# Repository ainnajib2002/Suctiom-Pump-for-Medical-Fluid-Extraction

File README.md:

## Suction-Pump-for-Medical-Fluid-Extraction

# Suction Pump for Medical Fluid Extraction

## Deskripsi Proyek
Suction Pump adalah alat medis untuk menghisap berbagai jenis cairan tubuh seperti darah, lendir, dan nanah selama prosedur medis. Proyek ini dirancang untuk menghasilkan suction pump berbasis mikrokontroler Arduino Mega dengan fitur IoT, keypad, dan LCD untuk pemantauan dan kontrol yang lebih baik.

---

## Fitur Utama
- **IoT Integration**: Pemantauan dan kontrol jarak jauh melalui cloud.
- **User Interface**: Keypad 4x4 dan LCD 20x4 untuk pengoperasian mudah.
- **Safety Design**: Bahan stainless steel untuk ketahanan dan kebersihan.

---

## Alat dan Bahan
| Komponen            | Deskripsi                                                                 |
|---------------------|---------------------------------------------------------------------------|
| **Mikrokontroler**  | Arduino Mega                                                            |
| **Sensor**          | MPX 5700 untuk tekanan                                                  |
| **Komponen Elektrik**| LCD 20x4, Keypad Matrix 4x4, Driver Motor L298N, Potentiometer         |
| **Komponen Mekanikal**| Bahan stainless steel untuk casing dan komponen mekanis lainnya       |

---

## Desain 3D

## Skema Rangkaian

---

## Panduan Instalasi dan Penggunaan
1. **Persiapan Hardware**: 
   - Rakit semua komponen sesuai skema.
   - Pastikan koneksi ke ESP32 dan sistem mekanik sudah sesuai.
2. **Instalasi Software**:
   - Gunakan Arduino IDE untuk mengunggah kode ke mikrokontroler.
3. **Konfigurasi IoT**:
   - Masukkan detail WiFi melalui keypad untuk koneksi cloud.
4. **Pengoperasian**:
   - Gunakan keypad untuk mengatur kecepatan dan parameter operasi.
   - Pantau informasi pada LCD 20x4.

---

## Sumber
- [Arduino IDE](https://www.arduino.cc/en/software)
- [Komponen ESP32](https://www.espressif.com/en/products/socs/esp32)

---

Jika desain ini sudah sesuai, saya dapat menambahkan detail lainnya. Silakan beri tahu!

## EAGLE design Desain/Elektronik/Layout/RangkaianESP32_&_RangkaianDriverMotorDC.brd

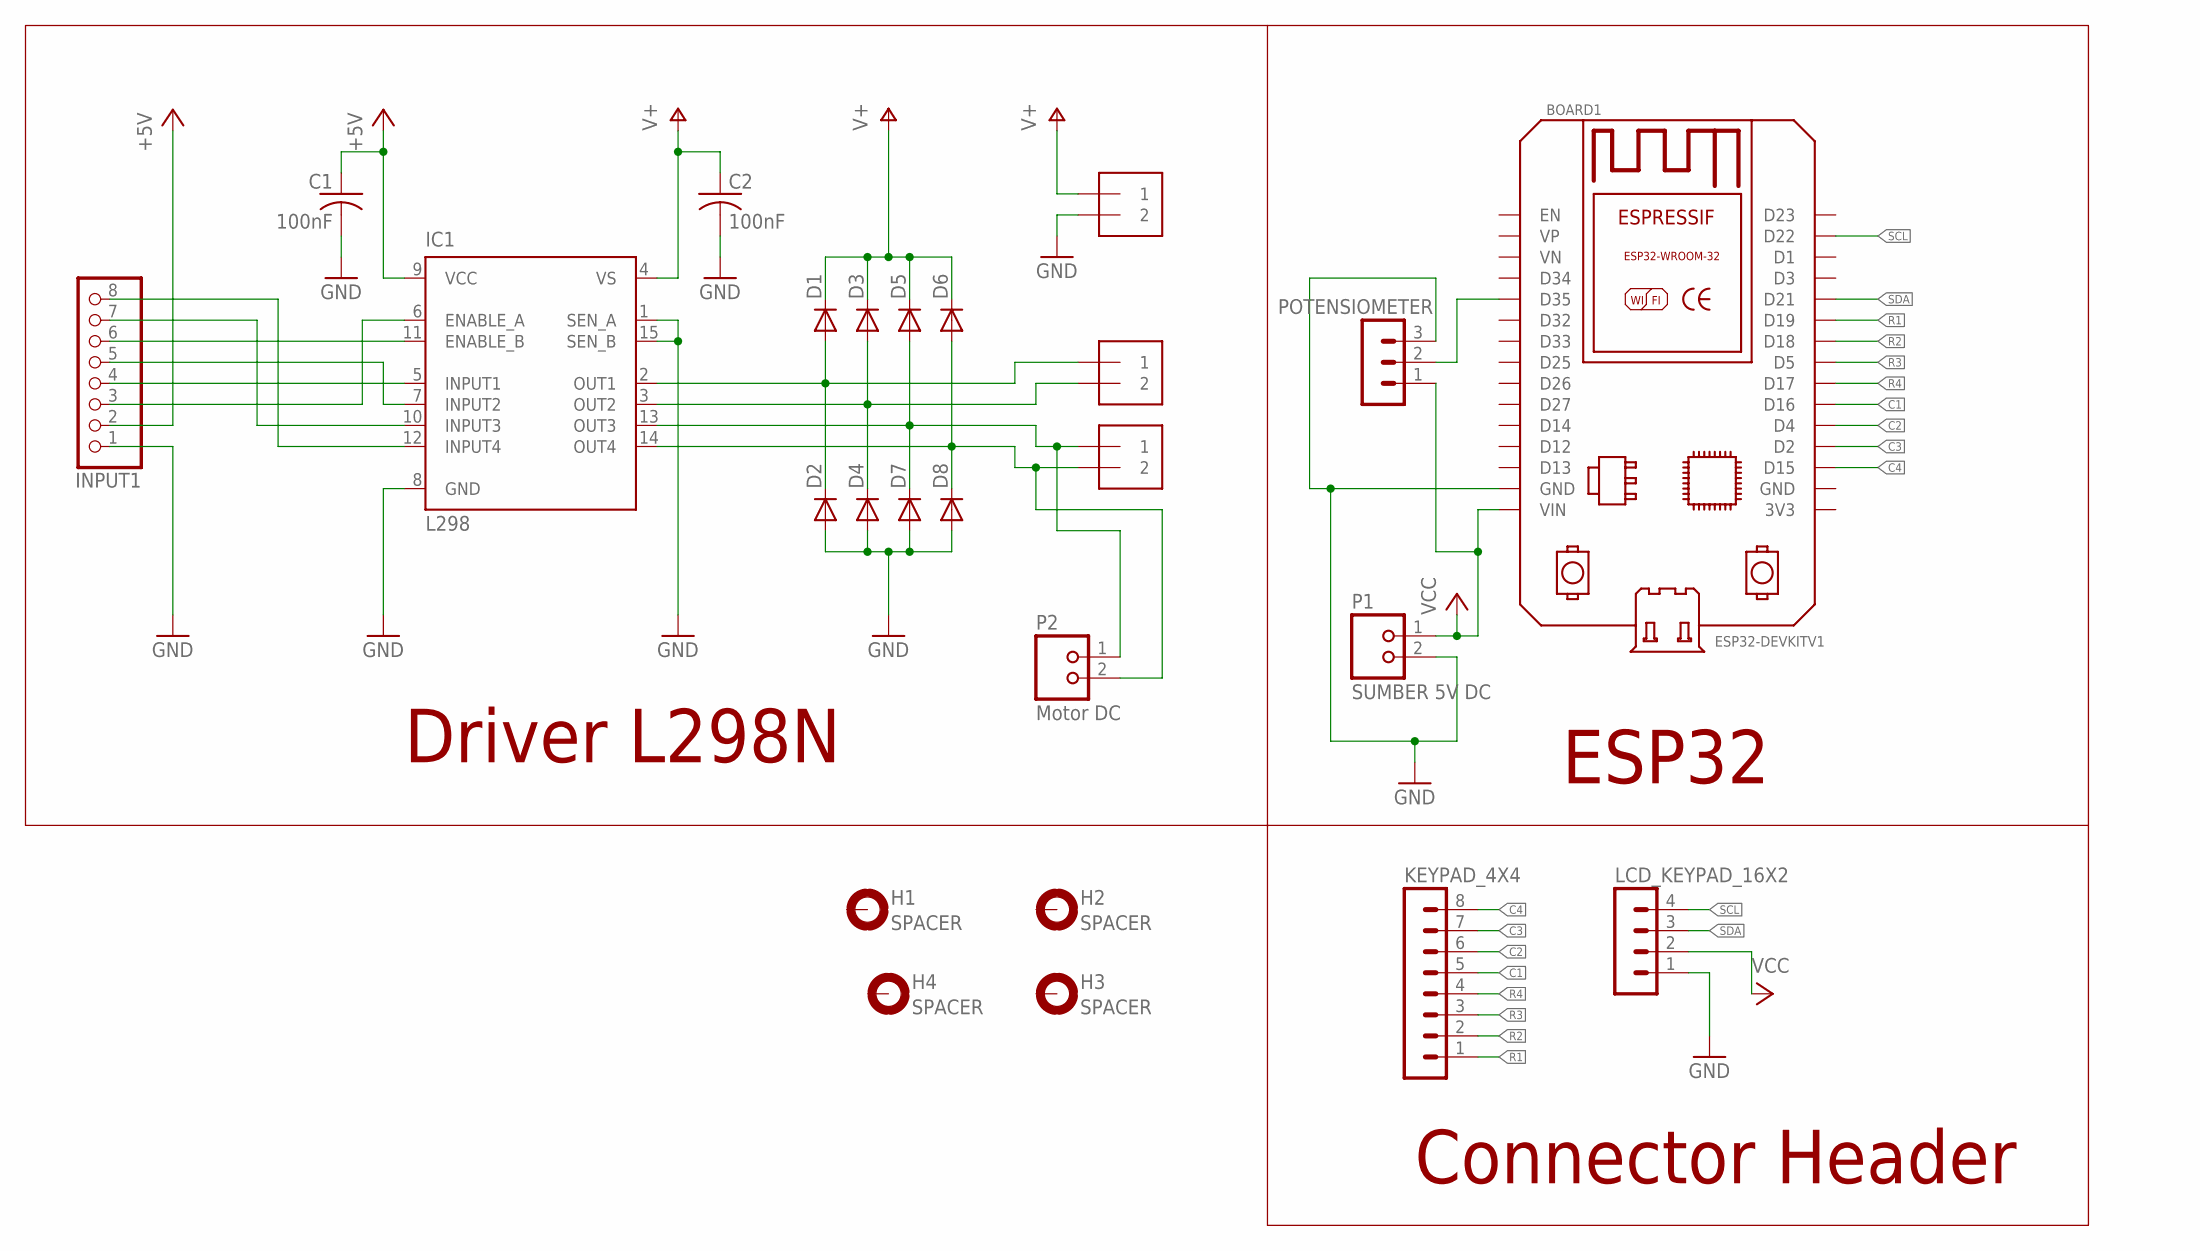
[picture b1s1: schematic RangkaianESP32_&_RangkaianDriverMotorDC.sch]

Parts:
BOARD1: ESP32DEVKITV1SHRIDATTDUDHAT; ESP32-DEVKITV1
C1, C2: 100nF; C050-024X044
D1, D2, D3, D4, D5, D6, D7, D8: DIODE-D-5; D-5
H1, H2, H3, H4: SPACER; 3,0-PAD
IC1: L298; MULTIWATT-15
INPUT1: PINHD-1X8; 1X08
KEYPAD_4X4: MA08-1
LCD_KEYPAD_16X2: MA04-1
OUTPUT1, OUTPUT2, OUTPUT3: 1X2-3.5MM
P1: SUMBER 5V DC; TERMINAL_2P
P2: Motor DC; TERMINAL_2P
POTENSIOMETER: MA03-1

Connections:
+5V: C1.1, IC1.9 (VCC), INPUT1.2
C1: BOARD1.D16, KEYPAD_4X4.5
C2: BOARD1.D4, KEYPAD_4X4.6
C3: BOARD1.D2, KEYPAD_4X4.7
C4: BOARD1.D15, KEYPAD_4X4.8
GND: BOARD1.GND, C1.2, C2.2, D2.A, D4.A, D7.A, D8.A, IC1.1 (SEN_A), IC1.8 (GND), IC1.15 (SEN_B), INPUT1.1, LCD_KEYPAD_16X2.1, OUTPUT1.2, P1.2, POTENSIOMETER.3
unnamed: D1.A, D2.C, IC1.2 (OUT1), OUTPUT2.1
unnamed: D3.A, D4.C, IC1.3 (OUT2), OUTPUT2.2
unnamed: D6.A, D8.C, IC1.14 (OUT4), OUTPUT3.2, P2.2
unnamed: D5.A, D7.C, IC1.13 (OUT3), OUTPUT3.1, P2.1
unnamed: IC1.5 (INPUT1), INPUT1.4
unnamed: IC1.7 (INPUT2), INPUT1.5
unnamed: IC1.6 (ENABLE_A), INPUT1.3
unnamed: IC1.11 (ENABLE_B), INPUT1.6
unnamed: IC1.10 (INPUT3), INPUT1.7
unnamed: IC1.12 (INPUT4), INPUT1.8
unnamed: BOARD1.D35, POTENSIOMETER.2
R1: BOARD1.D19, KEYPAD_4X4.1
R2: BOARD1.D18, KEYPAD_4X4.2
R3: BOARD1.D5, KEYPAD_4X4.3
R4: BOARD1.D17, KEYPAD_4X4.4
SCL: BOARD1.D22, LCD_KEYPAD_16X2.4
SDA: BOARD1.D21, LCD_KEYPAD_16X2.3
V+: C2.1, D1.C, D3.C, D5.C, D6.C, IC1.4 (VS), OUTPUT1.1
VCC: BOARD1.VIN, LCD_KEYPAD_16X2.2, P1.1, POTENSIOMETER.1

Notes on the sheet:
Driver L298N
ESP32
Connector Header

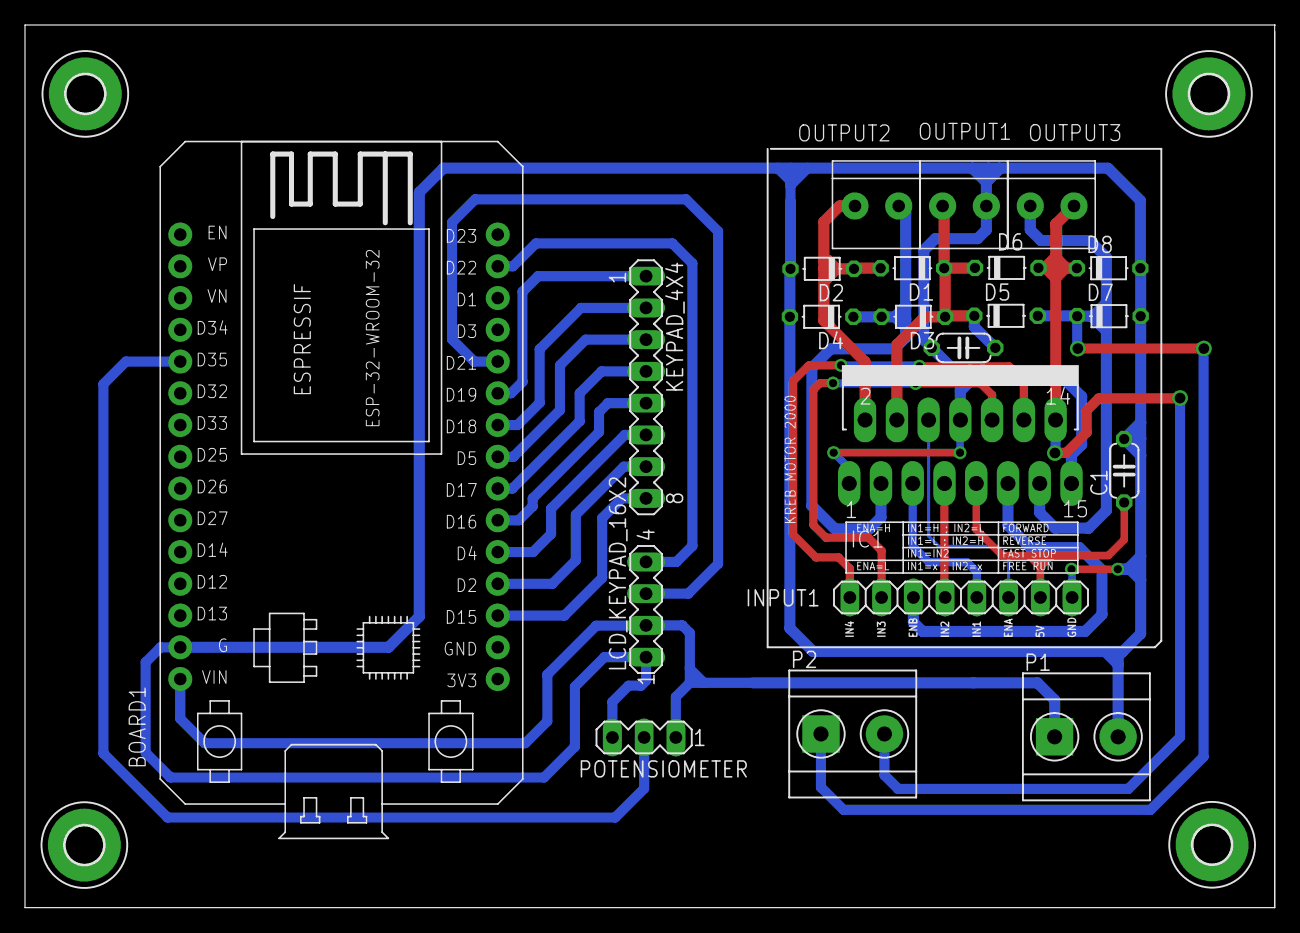
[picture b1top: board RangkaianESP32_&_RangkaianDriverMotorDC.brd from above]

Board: 2 copper layers, 100.0 x 70.6 mm, 25 parts (0 on the bottom side), 25 nets.

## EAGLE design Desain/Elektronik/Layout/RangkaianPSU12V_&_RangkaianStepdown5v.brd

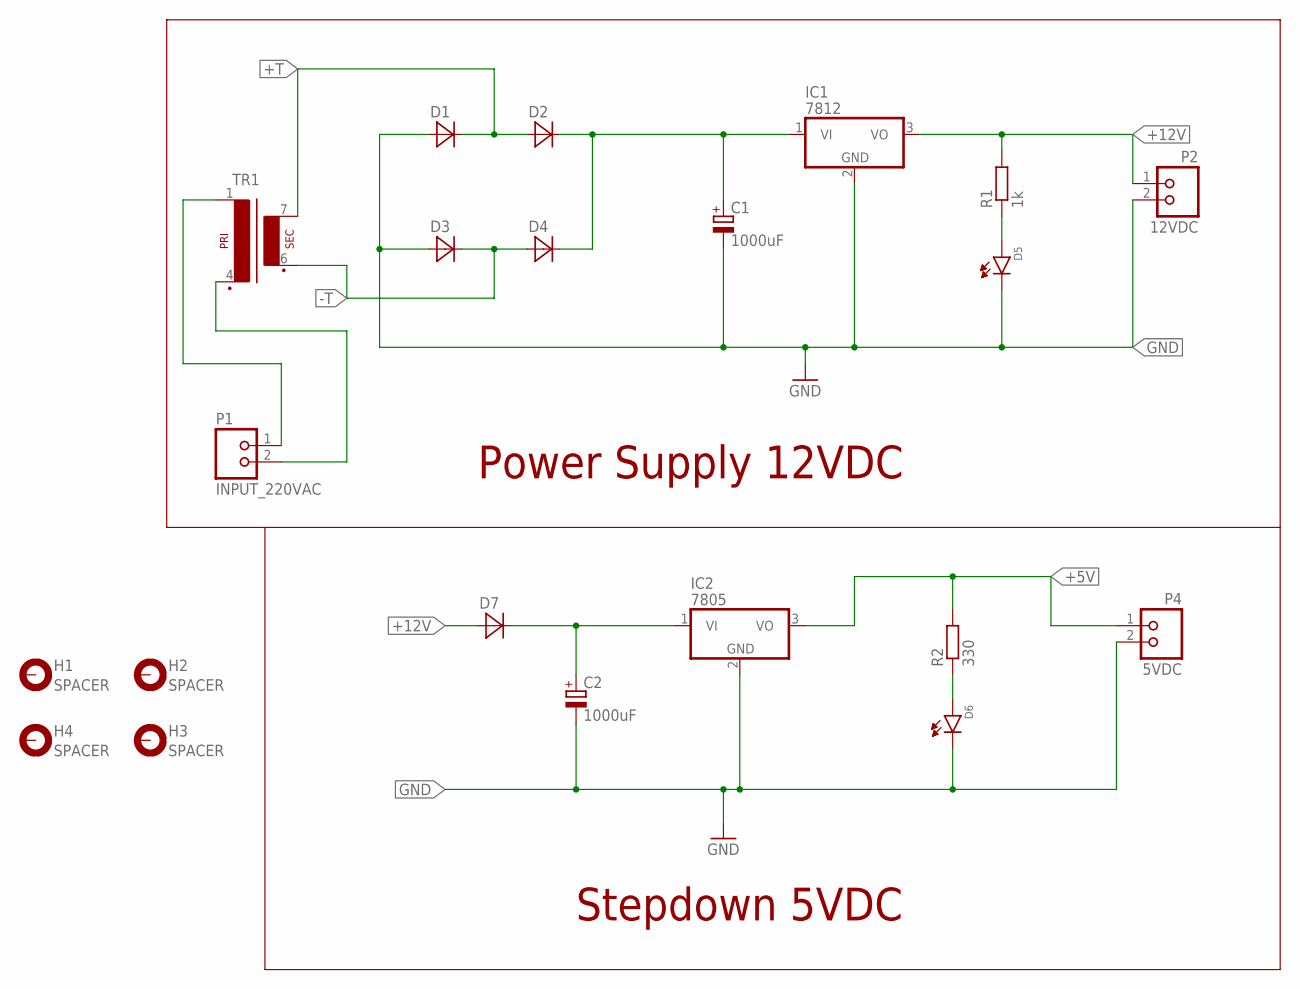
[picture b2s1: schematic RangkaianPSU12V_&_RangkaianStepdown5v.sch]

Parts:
C1, C2: 1000uF; E5-4
D1, D2, D3, D4, D7: 1N4148; DO35-10
D5, D6: LED-3MM; LED
H1, H2, H3, H4: SPACER; 3,0-PAD
IC1: 7812; TO220V
IC2: 7805; TO220V
P1: INPUT_220VAC; TERMINAL_2P
P2: 12VDC; TERMINAL_2P
P4: 5VDC; TERMINAL_2P
R1: 1k; AXIAL
R2: 330; AXIAL
TR1: EE20-1

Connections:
+5V: IC2.3 (VO), P4.1, R2.2
+12V: D7.A, IC1.3 (VO), P2.1, R1.2
+T: D1.K, D2.A, TR1.7 (S4)
-T: D3.K, D4.A, TR1.6 (S3)
GND: C1.-, C2.-, D1.A, D3.A, D5.2, D6.2, IC1.2 (GND), IC2.2 (GND), P2.2, P4.2
unnamed: P1.1, TR1.1
unnamed: P1.2, TR1.4 (P2)
unnamed: C1.+, D2.K, D4.K, IC1.1 (VI)
unnamed: D5.1, R1.1
unnamed: C2.+, D7.K, IC2.1 (VI)
unnamed: D6.1, R2.1

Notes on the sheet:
Power Supply 12VDC
Stepdown 5VDC

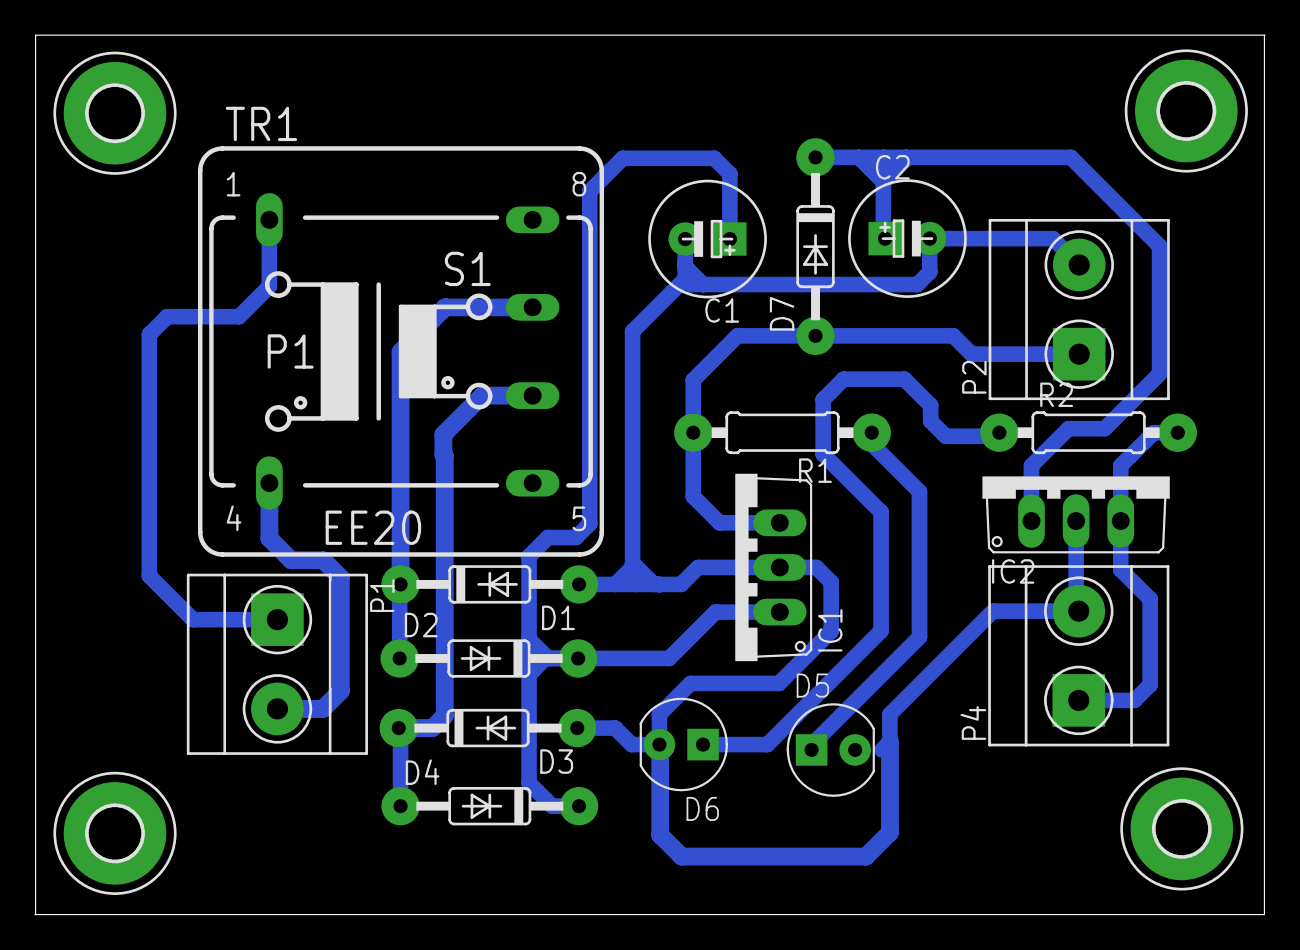
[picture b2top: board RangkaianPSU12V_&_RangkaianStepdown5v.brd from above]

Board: 2 copper layers, 70.0 x 50.1 mm, 21 parts (0 on the bottom side), 11 nets.

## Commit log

2024-12-27 Update README.md
    Mengganti Tampilan
2024-12-27 Update README.md
    Desain 3d
